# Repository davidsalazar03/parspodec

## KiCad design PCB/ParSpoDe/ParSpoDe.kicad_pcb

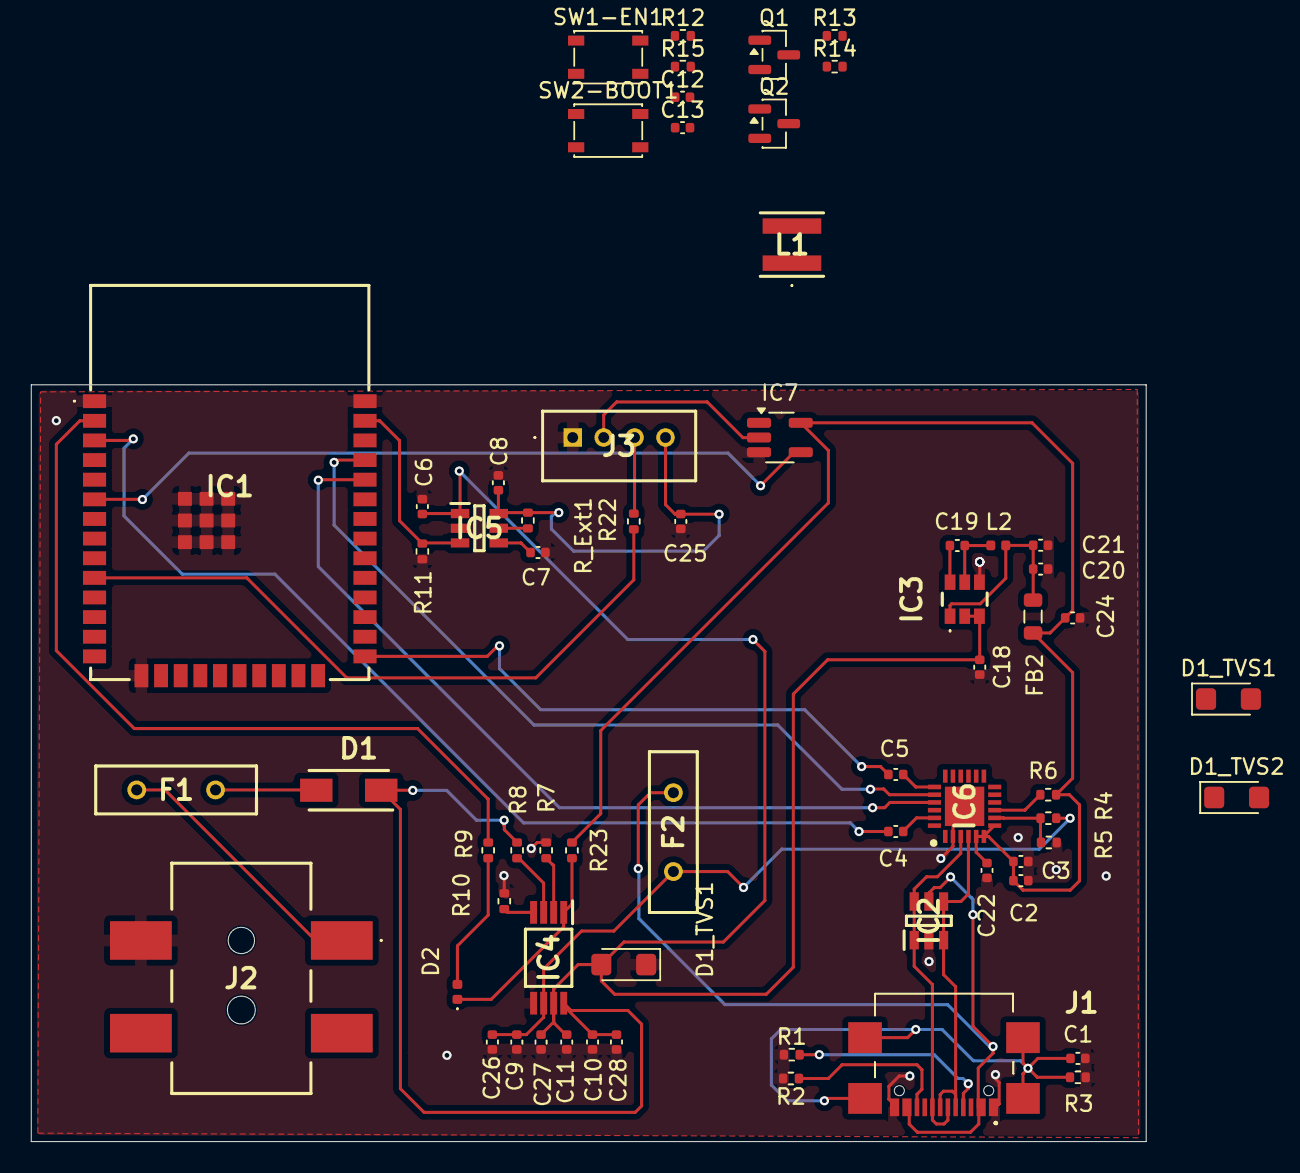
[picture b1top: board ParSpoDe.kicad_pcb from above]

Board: 2 copper layers, 72.1 x 49.0 mm, 65 parts (0 on the bottom side), 39 nets.

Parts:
C1, C7: 1n; C_0402_1005Metric
C2: 4.7u; C_0402_1005Metric
C3, C22, C24, C26, C27, C28: 0.1u; C_0402_1005Metric
C4, C5, C19: 100n; C_0402_1005Metric
C6, C9, C10, C18: 10u; C_0402_1005Metric
C8, C12, C13, C25: 1u; C_0402_1005Metric
C11, C20, C21: 22u; C_0402_1005Metric
D1: SS14_SCHTY_DIOD; DIOM5126X250N
D1_TVS1, D1_TVS1#2, D1_TVS2: SMF5V0A; D_SMF
D2: LED; LED_0402_1005Metric
F1, F2: MF-R075-2_POLYFUSE; MFR0752
FB2: 220 Ω @ 100 MHz, 0805, ≥2 A; L_0805_2012Metric
IC1: ESP32-WROOM-32E-N4; ESP32WROOM32EN4
IC2: USBLC6-2SC6_ESD_array; SOT95P280X145-6N
IC3: AP63203WU-7_BUCK; AP63203WU7
IC4: TPS2115APW_PWRMUX; SOP65P640X120-8N
IC5: TPS22918DBVR_LOADSWITCH; SOT95P280X145-6N
IC6: CP2102N-A02-GQFN24_USBC_UART_BRIDGE; QFN50P400X400X80-25N-D
IC7: SN74LVC1G17DBVR_LVLSHIFT; SOT-23-5_HandSoldering
J1: USB4110-GF-A_USBC_CONNECT; USB4110GFA
J2: PJ-002AH-SMT-TR_JACK5V; PJ002AHSMTTR
J3: B4B-PH-KL_LF__SN__4PIN_CONNECT; B4BPHKLLFSN
L1: 4.7uH; SRP4020FA4R7M
L2: 3.9u; L_0402_1005Metric
Q1, Q2: MMBT3904; SOT-23
R1, R2: 5.1K; R_0402_1005Metric
R3: 1M; R_0402_1005Metric
R4: 22.1k; R_0402_1005Metric
R5: 47.5k; R_0402_1005Metric
R6: 1k; R_0402_1005Metric
R7, R8, R11, R23: 100k; R_0402_1005Metric
R9: 1.5k; R_0402_1005Metric
R10: 250; R_0402_1005Metric
R12, R13, R14, R15: 10k; R_0402_1005Metric
R22: 100; R_0402_1005Metric
R_Ext1: 25; R_0402_1005Metric
SW1-EN1, SW2-BOOT1: SW_Push; SW_SPST_PTS810

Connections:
3V3: C2.1, C3.1, C22.2, C24.2, FB2.1, IC1.2 (3V3), IC6.5 (VIO), IC6.6 (VDD), IC6.7 (VREGIN), IC7.5 (VCC), R6.2, R9.2, R12.1, R15.1, R23.2
5V_IN: C6.2, C11.2, C18.1, C27.2, D1_TVS1#2.2 (A2), IC3.2 (EN), IC3.3 (VIN), IC4.7 (OUT), IC5.1 (VIN)
5V_SONAR: C8.2, C25.1, IC5.6 (VOUT), J3.4, R_Ext1.1
BARREL_5VIN: D1.2 (A), D1_TVS2.1 (A1), F1.1
BOOT_IO0: C5.1, C13.1, IC1.25 (IO0), Q2.3 (C), R15.2, SW2-BOOT1.1
DTR: IC6.23 (DTR), Q2.2 (E), R13.1
ECHO_ESP32: IC1.6 (IO34), IC7.4 (Y)
ECHO_LINE: IC7.2 (A), J3.2
EN_ESP: C4.1, C12.1, IC1.3 (EN), Q1.3 (C), R12.2, SW1-EN1.1
GND: C1.2, C2.2, C3.2, C6.1, C7.2, C8.1, C9.1, C10.2, C11.1, C12.2, C13.2, C18.2, C20.2, C21.1, C22.1, C24.1, C25.2, C26.1, C27.1, C28.2, D1_TVS1.2 (A2), D1_TVS1#2.1 (A1), D1_TVS2.2 (A2), IC1.1 (GND_1), IC1.15 (GND_2), IC1.38 (GND_3), IC1.39 (GND_4), IC1.40 (GND_5), IC1.41 (GND_6), IC1.42 (GND_7), IC1.43 (GND_8), IC1.44 (GND_9), IC1.45 (GND_10), IC1.46 (GND_11), IC1.47 (GND_12), IC2.2 (GND), IC3.4 (GND), IC4.5 (GND), IC5.2 (GND), IC6.2 (GND_1), IC6.25 (GND_2), IC7.3 (GND), J1.A1, J1.A12, J1.B1, J1.B12, J2.2, J3.1, R1.1, R2.2, R3.2, R5.2, R7.1, R10.2, R11.1, SW1-EN1.2, SW2-BOOT1.2
IN1_JACK: C10.1, C28.1, D1.1 (K), IC4.8 (IN1), R8.1
LOADSW_EN: IC1.37 (IO23), IC5.3 (ON), R11.2
unnamed: D2.2 (A), R9.1
unnamed: D2.1 (K), IC4.1 (STAT), R23.1
unnamed: F1.2, J2.1
unnamed: IC1.10 (IO25), R22.1
unnamed: C19.1, IC3.6 (BST)
unnamed: C20.1, C21.2, FB2.2, IC3.1 (FB), L1.2, L2.2
unnamed: C19.2, IC3.5 (SW), L1.1, L2.1
unnamed: IC4.2 (D0), R7.2
unnamed: IC4.3 (D1), R8.2
unnamed: IC4.4 (ILIM), R10.1
unnamed: C7.1, IC5.4 (CT)
unnamed: IC5.5 (QOD), R_Ext1.2
unnamed: IC6.9 (RSTB), R6.1
unnamed: IC6.8 (VBUS), R4.2, R5.1
unnamed: J1.A5, R1.2
unnamed: J1.B5, R2.1
unnamed: Q1.1 (B), R13.2
unnamed: Q2.1 (B), R14.2
RTS: IC6.19 (RTS), Q1.2 (E), R14.1
SHIELD: C1.1, J1.MP1, J1.MP2, J1.MP3, J1.MP4, R3.1
TRIG_ESP32: J3.3, R22.2
U0RXD: IC1.34 (RXD0), IC6.21 (TXD)
U0TXD: IC1.35 (TXD0), IC6.20 (RXD)
USB5V_IN: C9.2, C26.2, D1_TVS1.1 (A1), F2.2, IC4.6 (IN2), R4.1
USB5V_RAW: F2.1, IC2.5 (VBUS), J1.A4, J1.A9, J1.B4, J1.B9
USB_D_N: IC2.3 (I/O2_1), IC2.4 (I/O2_2), IC6.4 (D-), J1.A7, J1.B7
USB_D_P: IC2.1 (I/O1_1), IC2.6 (I/O1_2), IC6.3 (D+), J1.A6, J1.B6
